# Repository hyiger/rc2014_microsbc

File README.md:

# RC2014 Compatible Z80 SBC card
A complete Z80 based SBC in a RC2014 card form factor

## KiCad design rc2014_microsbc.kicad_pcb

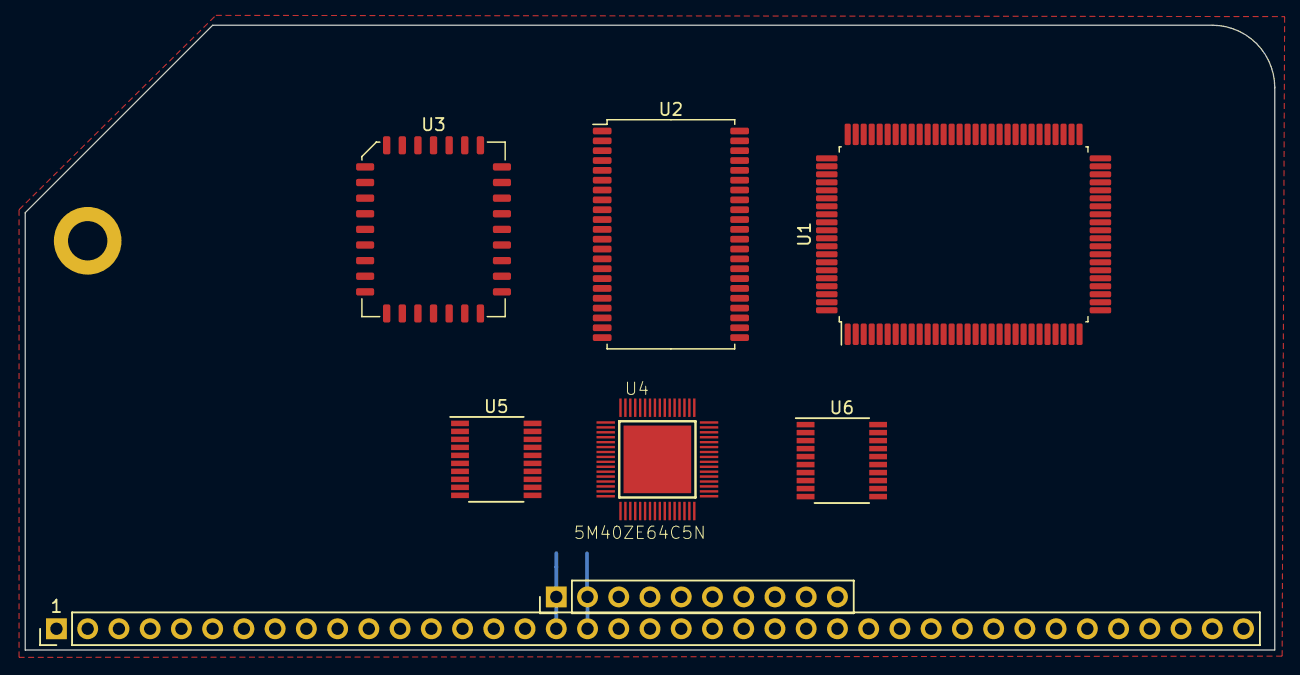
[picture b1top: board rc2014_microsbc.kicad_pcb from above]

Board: 2 copper layers, 101.6 x 50.8 mm, 10 parts (1 on the bottom side), 4 nets.

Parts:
C1: 100nF; C_0805_2012Metric
J1: Z80 Bus; PinHeader_1x39_P2.54mm_Vertical
J2: Pro Bus; PinHeader_1x10_P2.54mm_Vertical
J4: M3 Mounting Hole; MountingHole_3.2mm_M3_ISO14580_Pad
U1: Z84C1516FSG; PQFP-100_14x20mm_P0.65mm
U2: IS61C5128AL-10TLI; TSOP-II-44_10.16x18.41mm_P0.8mm
U3: AT27C040; PLCC-32_11.4x14.0mm_P1.27mm
U4: 5M40ZE64C5N; QFP40P900X900X120-65N
U5, U6: SN74LVC245AN; TSSOP-20_4.4x6.5mm_P0.65mm

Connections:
5V: C1.1, J1.18, J2.2, U1.41, U1.90
GND: C1.2, J1.17, J2.1, J4.1, U1.16, U1.64
unnamed: U2.11, U2.33
unnamed: U2.12, U2.34

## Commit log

2019-05-29 First version
